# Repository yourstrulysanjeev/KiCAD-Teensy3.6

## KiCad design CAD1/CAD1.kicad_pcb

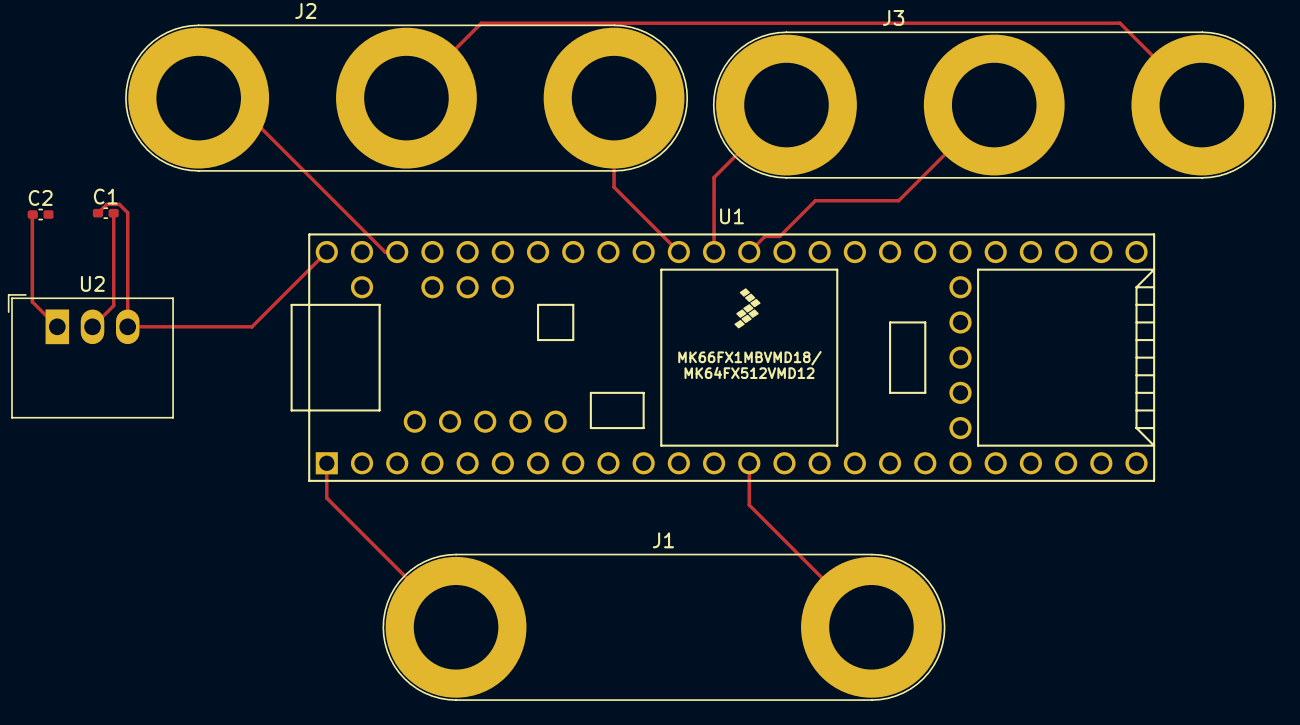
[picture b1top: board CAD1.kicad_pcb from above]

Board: 2 copper layers, 7 parts (0 on the bottom side), 10 nets.

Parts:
C1, C2: 1u; C_0402_1005Metric_Pad0.74x0.62mm_HandSolder
J1: Input Connector; Banana_Jack_2Pin
J2: Connector for Servo; Banana_Jack_3Pin
J3: Connector for DC; Banana_Jack_3Pin
U1: Teensy; Teensy35_36
U2: R-78B5.0-2.0; Converter_DCDC_RECOM_R-78B-2.0_THT

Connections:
+9V: C2.1, U2.1
GND: C1.2, C2.2, U2.2
unnamed: C1.1, U1.53, U2.3
unnamed: J1.1, U1.1
unnamed: J1.2, U1.13
unnamed: J2.1, U1.51
unnamed: J2.2, J3.3
unnamed: J2.3, U1.43
unnamed: J3.1, U1.42
unnamed: J3.2, U1.41

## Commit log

2021-06-05 Create x
